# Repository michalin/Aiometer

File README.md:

# All-In-One Meter
## What It Is
A device that can be (almost) everything. Clock, calendar, stock ticker or weather station. The data is retrieved public REST APIs over the Internet and displayed on VFD tubes. REST stands for REpresentational State Transfer, API for Application Programming Interface. This refers to a programming interface that describes the communication between applications (e.g. apps or IoT devices) and web services in networks. You can find a good choice of public REST APIs here: https://github.com/public-apis/public-apis   
An ESP32 handles both the connection via REST APIs and the control of the VFD tubes. The APIs to be accessed are configured in a JSON file. This provides the greatest possible flexibility. The device is controlled by a rotary encoder. This allows to select a specific web service (or its REST API) as well as the individual data points returned by it.   
There are still large stocks of the soviet VFD tubes type IV-11, so they can be purchased cheaply via Ebay or online stores. Under the tubes are WS2812 compatible RGB LEDs, which provide a nice color accent.

## Configuration
The device's configuration can be modified by editing the 'data/settings.json' file, which allows customization of the following parameters:
- WLAN SSID and password
- Hostname for remote access
- NTP server address
- Time zone
- Date and time format using standard date and time format specifiers
- LED colors while connecting to WLAN or waiting for server response
- Array with API queries:
  - Alias: String displayed on the tubes when a query is selected
  - Refresh: Interval at which data is polled in seconds
  - URL: API URL
  - GET: Array with the values of interest
- Array with APIs of devices to control
  - Alias: String displayed on the tubes when a query is selected
  - URL: URL of device to control
  - Value: Value to send to the device after it has been selected
  - Step, Min, Max: How the value changes, when the encoder is turned

The settings.json file can be easily uploaded to the SPIFFs filesystem of the ESP32 using the provided batch file "spiffs.bat".

## Usage
### Query APIs
To select a query, press and hold the rotary encoder while turning it until the desired query's alias appears, then release it. Rotate the rotary encoder to choose a data item returned by the query.
### Control APIs
To modify the LED color or brightness, or control an IoT device, quickly press the rotary encoder twice within one second. Press and hold the encoder while turning it until the alias of the desired device to control is displayed on the tubes, then release it. Rotating the encoder sends the value to the device.

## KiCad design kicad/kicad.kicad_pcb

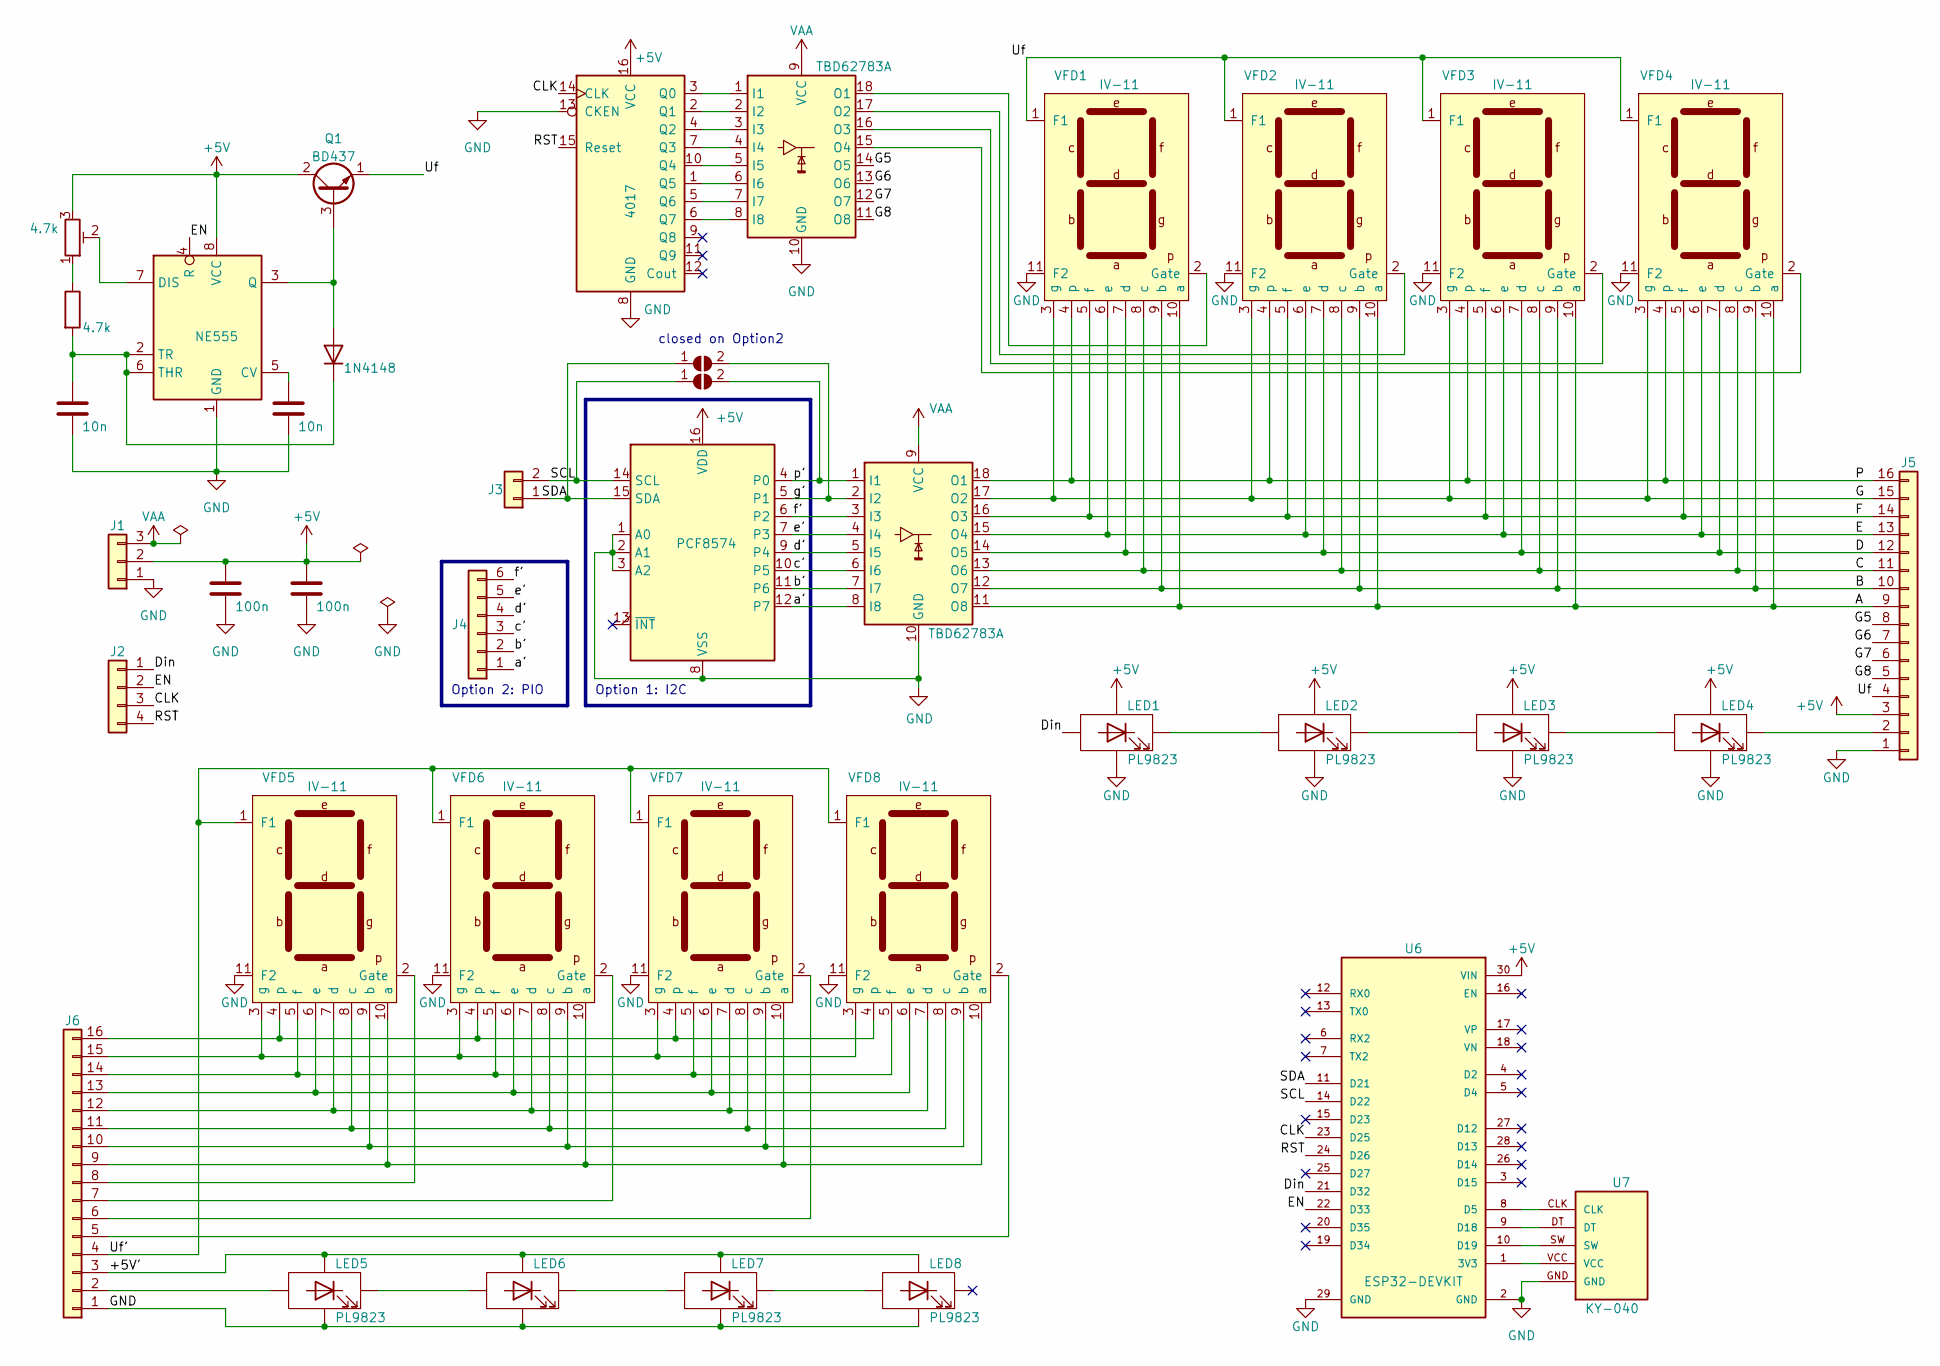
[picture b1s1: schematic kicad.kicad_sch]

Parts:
C1, C2: 10n; C_Disc_D3.4mm_W2.1mm_P2.50mm
C3, C4: 100n; C_Disc_D5.0mm_W2.5mm_P2.50mm
D1: 1N4148; D_DO-35_SOD27_P7.62mm_Horizontal
J1: Conn_01x03; Molex_KK-254_AE-6410-03A_1x03_P2.54mm_Vertical
J2: Conn_01x04; Molex_KK-254_AE-6410-04A_1x04_P2.54mm_Vertical
J3: Conn_01x02; conn_I2C
J4: Conn_01x06; conn_option2_PIO
J5, J6: Conn_01x16; conn_extender
JP1, JP2: SolderJumper_2_Open; SolderJumper-2_P1.3mm_Open_RoundedPad1.0x1.5mm
LED1, LED2, LED3, LED4, LED5, LED7, LED8: PL9823; LED_PL9823-F5
LED6: LED-PL9823; LED_PL9823-F5
Q1: BD437; TO-126-3
R1: 4.7k; R_Axial_DIN0207_L6.3mm_D2.5mm_P7.62mm_Horizontal
RV1: 4.7k; Potentiometer_Piher_PT-10-V10_Vertical
U1: NE555; DIP-8_W7.62mm_Socket
U2: 4017; DIP-16_W7.62mm_Socket
U3, U5: TBD62783A; DIP-18_W7.62mm_Socket
U4: PCF8574; DIP-16_W7.62mm_Socket
U6: ESP32-DEVKIT; MODULE_ESP32_DEVKIT_V1; PARTREV N/A
U7: KY-040; KY-040-PORT
VFD1, VFD2, VFD3, VFD4, VFD5, VFD6, VFD7, VFD8: IV-11; VFD-IV11

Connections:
+5V: C3.1, C4.1, J1.2, J5.3, LED1.3 (VDD), LED2.3 (VDD), LED3.3 (VDD), LED4.3 (VDD), Q1.2 (C), RV1.3, U1.8 (VCC), U2.16 (VCC), U4.16 (VDD), U6.30 (VIN)
/+5V': J6.3, LED5.3 (VDD), LED6.3 (VDD), LED7.3 (VDD), LED8.3 (VDD)
/A: J5.9, U5.11 (O8), VFD1.10 (a), VFD2.10 (a), VFD3.10 (a), VFD4.10 (a)
/B: J5.10, U5.12 (O7), VFD1.9 (b), VFD2.9 (b), VFD3.9 (b), VFD4.9 (b)
/C: J5.11, U5.13 (O6), VFD1.8 (c), VFD2.8 (c), VFD3.8 (c), VFD4.8 (c)
/CLK: J2.3, U2.14 (CLK), U6.23 (D25)
/D: J5.12, U5.14 (O5), VFD1.7 (d), VFD2.7 (d), VFD3.7 (d), VFD4.7 (d)
/Din: J2.1, LED1.4 (Din), U6.21 (D32)
/E: J5.13, U5.15 (O4), VFD1.6 (e), VFD2.6 (e), VFD3.6 (e), VFD4.6 (e)
/EN: J2.2, U1.4 (R), U6.22 (D33)
/F: J5.14, U5.16 (O3), VFD1.5 (f), VFD2.5 (f), VFD3.5 (f), VFD4.5 (f)
/G: J5.15, U5.17 (O2), VFD1.3 (g), VFD2.3 (g), VFD3.3 (g), VFD4.3 (g)
/G5: J5.8, U3.14 (O5)
/G6: J5.7, U3.13 (O6)
/G7: J5.6, U3.12 (O7)
/G8: J5.5, U3.11 (O8)
/P: J5.16, U5.18 (O1), VFD1.4 (p), VFD2.4 (p), VFD3.4 (p), VFD4.4 (p)
/RST: J2.4, U2.15 (Reset), U6.24 (D26)
/SCL: J3.2, JP2.1 (A), U4.14 (SCL), U6.14 (D22)
/Uf: J5.4, Q1.1 (E), VFD1.1 (F1), VFD2.1 (F1), VFD3.1 (F1), VFD4.1 (F1)
/Uf': J6.4, VFD5.1 (F1), VFD6.1 (F1), VFD7.1 (F1), VFD8.1 (F1)
/a': J4.1, U4.12 (P7), U5.8 (I8)
/b': J4.2, U4.11 (P6), U5.7 (I7)
/c': J4.3, U4.10 (P5), U5.6 (I6)
/d': J4.4, U4.9 (P4), U5.5 (I5)
/e': J4.5, U4.7 (P3), U5.4 (I4)
/f': J4.6, U4.6 (P2), U5.3 (I3)
/g': JP1.2 (B), U4.5 (P1), U5.2 (I2)
/p': JP2.2 (B), U4.4 (P0), U5.1 (I1)
GND: C1.2, C2.2, C3.2, C4.2, J1.1, J5.1, J6.1, LED1.2 (GND), LED2.2 (GND), LED3.2 (GND), LED4.2 (GND), LED5.2 (GND), LED6.2 (GND), LED7.2 (GND), LED8.2 (GND), U1.1 (GND), U2.8 (GND), U2.13 (CKEN), U3.10 (GND), U4.1 (A0), U4.2 (A1), U4.3 (A2), U4.8 (VSS), U5.10 (GND), U6.2 (GND), U6.29 (GND), U7.GND, VFD1.11 (F2), VFD2.11 (F2), VFD3.11 (F2), VFD4.11 (F2), VFD5.11 (F2), VFD6.11 (F2), VFD7.11 (F2), VFD8.11 (F2)
unnamed: D1.2 (A), Q1.3 (B), U1.3 (Q)
unnamed: C2.1, D1.1 (K), R1.2, U1.2 (TR), U1.6 (THR)
unnamed: J3.1, JP1.1 (A), U4.15 (SDA), U6.11 (D21)
unnamed: J5.2, LED4.1 (Dout)
unnamed: J6.2, LED5.4 (Din)
unnamed: J6.5, VFD8.2 (Gate)
unnamed: J6.6, VFD7.2 (Gate)
unnamed: J6.7, VFD6.2 (Gate)
unnamed: J6.8, VFD5.2 (Gate)
unnamed: J6.9, VFD5.10 (a), VFD6.10 (a), VFD7.10 (a), VFD8.10 (a)
unnamed: J6.10, VFD5.9 (b), VFD6.9 (b), VFD7.9 (b), VFD8.9 (b)
unnamed: J6.11, VFD5.8 (c), VFD6.8 (c), VFD7.8 (c), VFD8.8 (c)
unnamed: J6.12, VFD5.7 (d), VFD6.7 (d), VFD7.7 (d), VFD8.7 (d)
unnamed: J6.13, VFD5.6 (e), VFD6.6 (e), VFD7.6 (e), VFD8.6 (e)
unnamed: J6.14, VFD5.5 (f), VFD6.5 (f), VFD7.5 (f), VFD8.5 (f)
unnamed: J6.15, VFD5.3 (g), VFD6.3 (g), VFD7.3 (g), VFD8.3 (g)
unnamed: J6.16, VFD5.4 (p), VFD6.4 (p), VFD7.4 (p), VFD8.4 (p)
unnamed: LED1.1 (Dout), LED2.4 (Din)
unnamed: LED2.1 (Dout), LED3.4 (Din)
unnamed: LED3.1 (Dout), LED4.4 (Din)
unnamed: LED5.1 (Dout), LED6.4 (Din)
unnamed: LED6.1 (Dout), LED7.4 (Din)
unnamed: LED7.1 (Dout), LED8.4 (Din)
unnamed: R1.1, RV1.1
unnamed: C1.1, U1.5 (CV)
unnamed: RV1.2, U1.7 (DIS)
unnamed: U2.3 (Q0), U3.1 (I1)
unnamed: U2.2 (Q1), U3.2 (I2)
unnamed: U2.4 (Q2), U3.3 (I3)
unnamed: U2.7 (Q3), U3.4 (I4)
unnamed: U2.10 (Q4), U3.5 (I5)
unnamed: U2.1 (Q5), U3.6 (I6)
unnamed: U2.5 (Q6), U3.7 (I7)
unnamed: U2.6 (Q7), U3.8 (I8)
unnamed: U3.18 (O1), VFD1.2 (Gate)
unnamed: U3.17 (O2), VFD2.2 (Gate)
unnamed: U3.16 (O3), VFD3.2 (Gate)
unnamed: U3.15 (O4), VFD4.2 (Gate)
unnamed: U6.1 (3V3), U7.VCC
unnamed: U6.8 (D5), U7.CLK
unnamed: U6.9 (D18), U7.DT
unnamed: U6.10 (D19), U7.SW
VAA: J1.3, U3.9 (VCC), U5.9 (VCC)

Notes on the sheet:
closed on Option2
Option 2: PIO
Option 1: I2C

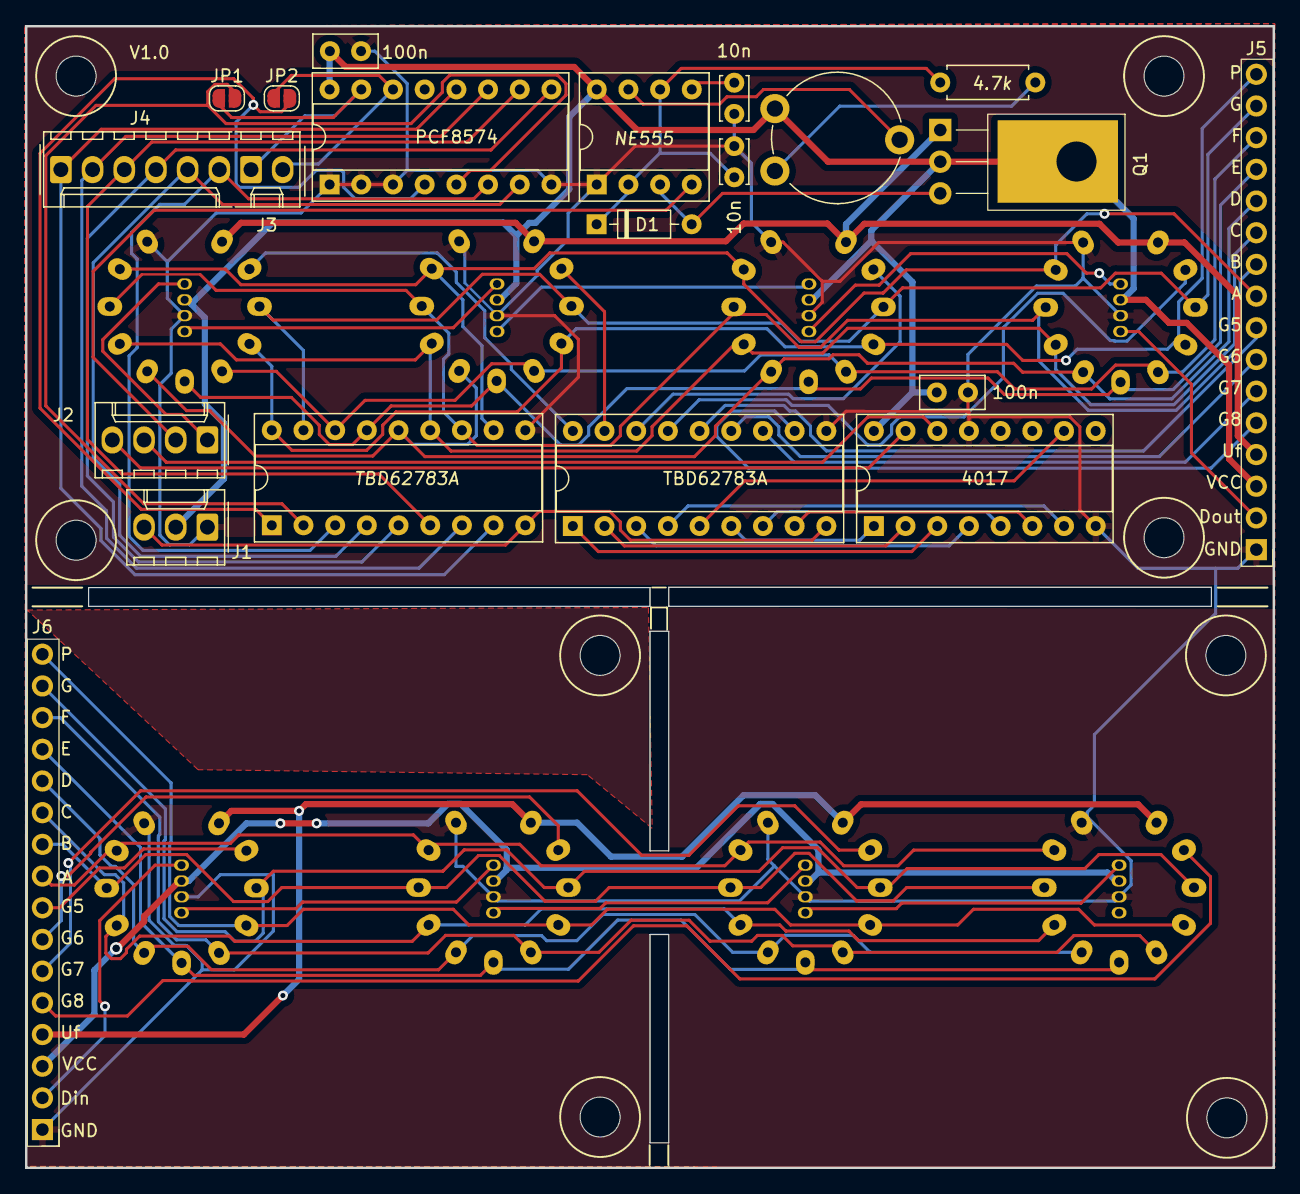
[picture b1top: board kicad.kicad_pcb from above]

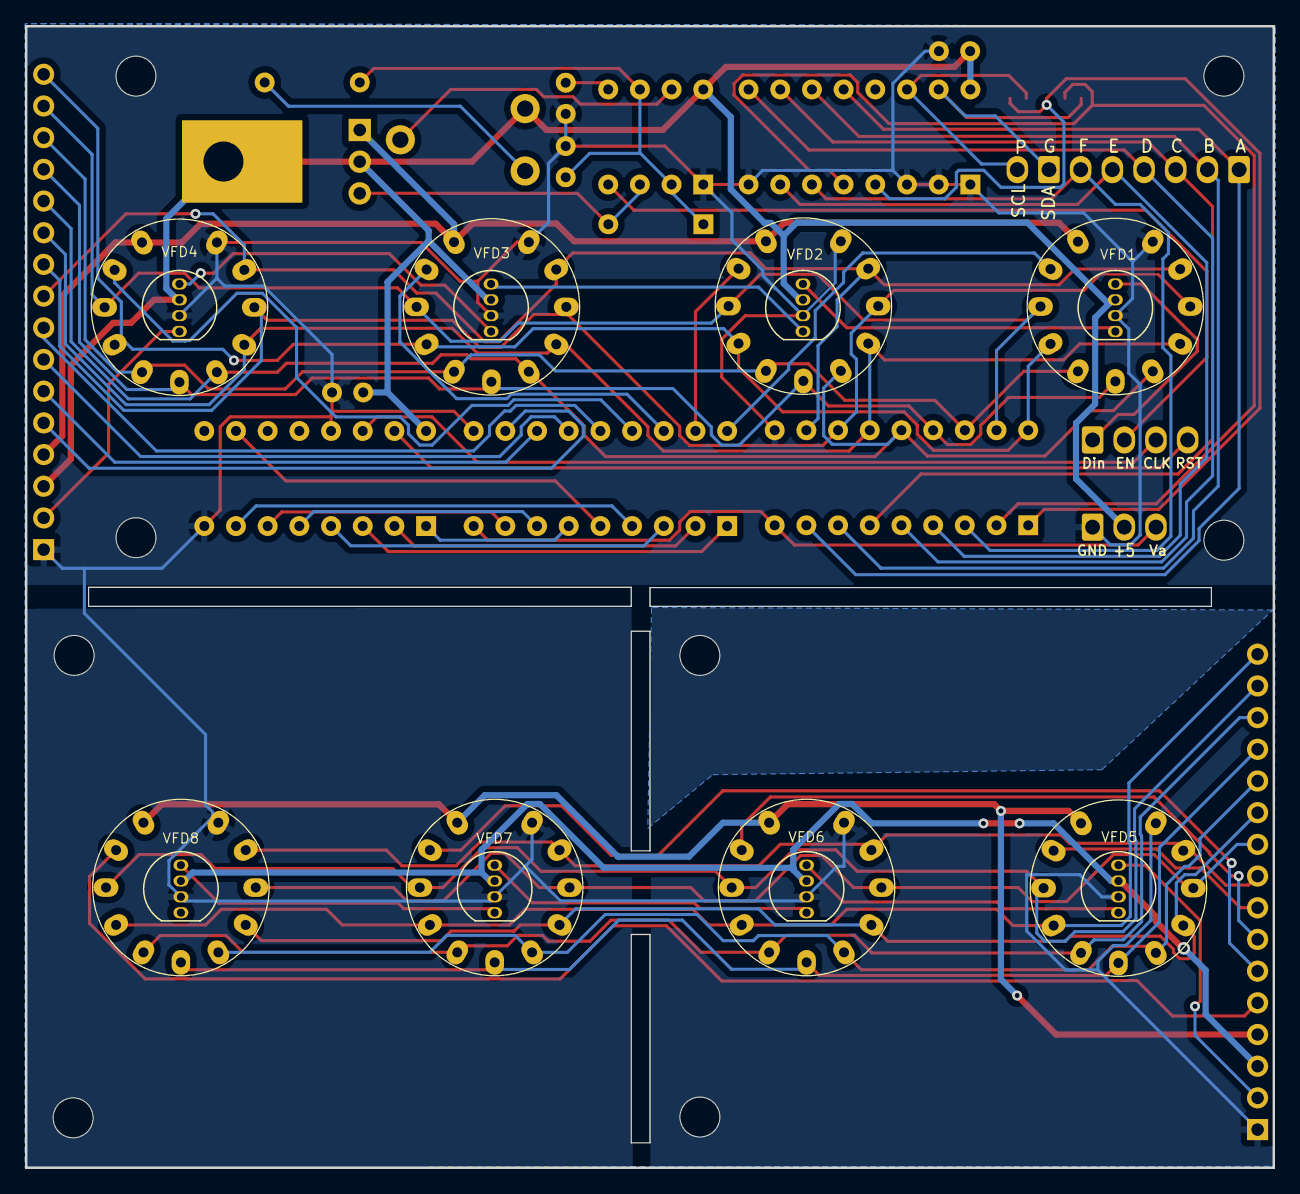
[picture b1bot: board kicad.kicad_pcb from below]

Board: 2 copper layers, 100.0 x 91.5 mm, 45 parts (16 on the bottom side), 69 nets.

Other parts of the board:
M1, M2, M3, M4, M6, M7, M9, M10: MountingHole_3.2mm_M3
